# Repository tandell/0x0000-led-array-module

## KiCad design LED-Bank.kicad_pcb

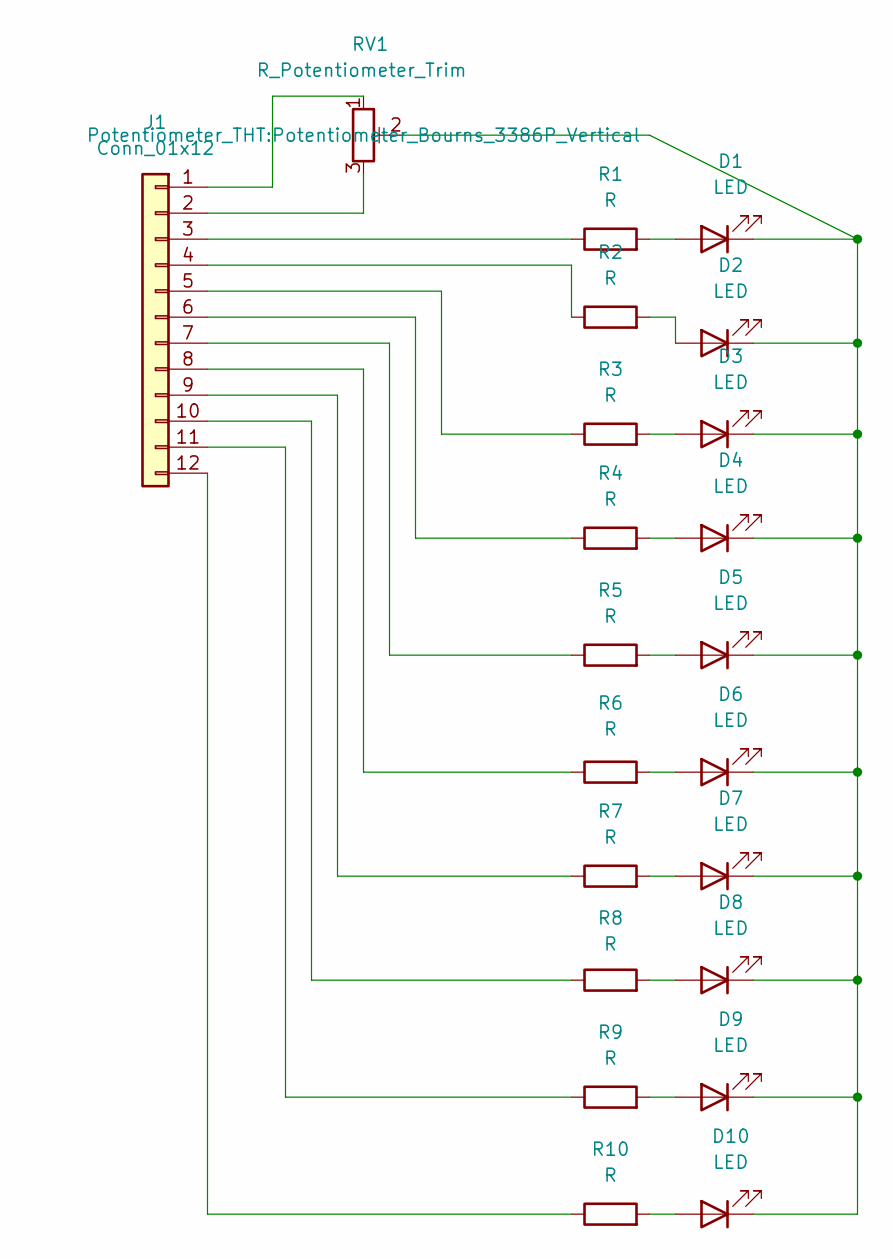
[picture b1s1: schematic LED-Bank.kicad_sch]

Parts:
D1, D2, D3, D4, D5, D6, D7, D8, D9, D10: LED; LED_D3.0mm
J1: Conn_01x12; PinHeader_1x12_P2.54mm_Horizontal
R1, R2, R3, R4, R5, R6, R7, R8, R9, R10: R; R_Axial_DIN0207_L6.3mm_D2.5mm_P7.62mm_Horizontal
RV1: R_Potentiometer_Trim; Potentiometer_Bourns_3386P_Vertical

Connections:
unnamed: D2.2 (A), R2.2
unnamed: D5.2 (A), R5.2
unnamed: D7.2 (A), R7.2
unnamed: J1.1, RV1.1
unnamed: J1.2, RV1.3
unnamed: J1.3, R1.1
unnamed: J1.4, R2.1
unnamed: J1.5, R3.1
unnamed: J1.6, R4.1
unnamed: J1.7, R5.1
unnamed: J1.8, R6.1
unnamed: J1.9, R7.1
unnamed: J1.10, R8.1
unnamed: J1.11, R9.1
unnamed: J1.12, R10.1
unnamed: D1.2 (A), R1.2
unnamed: D3.2 (A), R3.2
unnamed: D4.2 (A), R4.2
unnamed: D6.2 (A), R6.2
unnamed: D8.2 (A), R8.2
unnamed: D9.2 (A), R9.2
unnamed: D10.2 (A), R10.2
unnamed: D1.1 (K), D2.1 (K), D3.1 (K), D4.1 (K), D5.1 (K), D6.1 (K), D7.1 (K), D8.1 (K), D9.1 (K), D10.1 (K), RV1.2

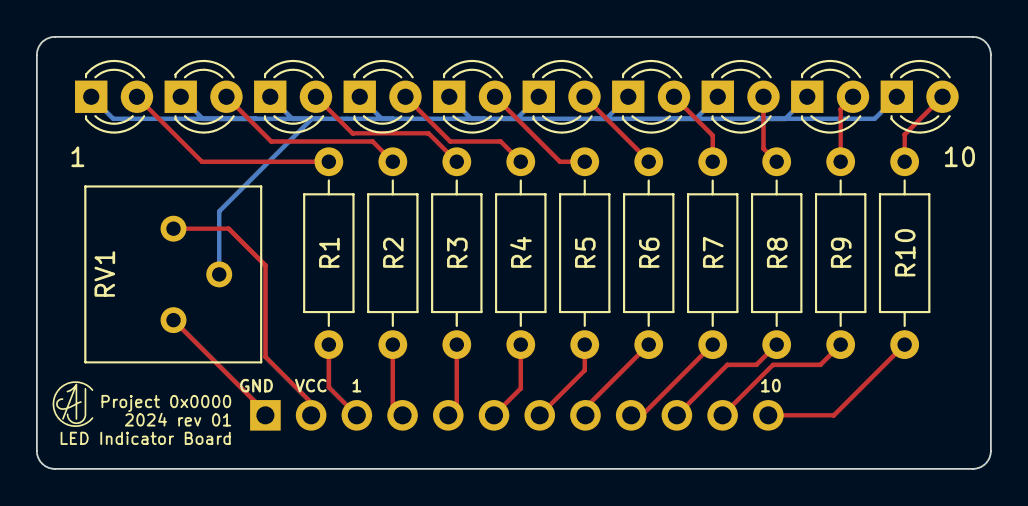
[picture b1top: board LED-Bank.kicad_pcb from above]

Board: 2 copper layers, 53.0 x 24.0 mm, 22 parts (1 on the bottom side), 23 nets.

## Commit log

2024-09-19 LED Bank Initial Commit
